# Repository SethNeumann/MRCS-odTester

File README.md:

# MRCS-odTester
## License: Creative Commons Attribution-NonCommercial-ShareAlike

A simple bench test board for Chubb\'s DCC-OD and MRCS\' cpOD detectors.

### Theory:

This board is designed to be a bench test unit for Chubb\'s DCCOD style
detectors. A board is inserted into the test pins and the three buttons
are pressed in sequence while observing the \"detected\" LED. A \"good\"
board will light up with both the \"low\" and \"normal\" button presses,
but not the \"high\" one. The DCCOD sensitivity can be adjusted in the
jig to give the desired behavior.

A local test track can be optionally connected that enables the testing
of specific locomotives and rolling stock simply by placing them on the
track.

The values for R1, R2 and R3 should be chosen for the layout and
locomotives in use - N-scale\'s small highly efficient motors will draw
less current than a O- or G-scale, and will require greater sensitivity.
Your wheelsets may provide 10K or 100K resistors, which should also
inform your choices. The values below are astarting point; feel free to
experiment. There is nothing wrong with choosing 100K as \"normal\" and
150K as \"too high\" as long as your choice of \"turns\" thru the
DCCOD\'s pulse transformer can provide the detection. Start with
\"normal\" matching your wheelset/rolling stock resistors, \"low\" being
half of that, and high being 2x to 10x of normal\...

Validate that your DCCOD can actually detect your chosen values by
adjusting its potentiometer to its mose sensitive position and observing
that the detected LED lights when the buttons are pressed.

Usage:

  -   Plug a DCCOD board to the DetectorTester.
  -   Connect to a 12v DC regulated power supply.
  -   Connect the output of a DCC booster to the DCC connector
  -   Press one of the pushbuttons to place a detectable load resistance across the simulated \"track\" for the detector to see
    -   Sensitivity test values (choose to match your givens and druthers)
    -   5K resistance (\~3mA)
    -   10K resistance (\~1.5mA)
    -   100K resistance (\~0.15mA)
    -   150K resistance (\~0.1mA)

Use the following table to diagnose/adjust based on the whether the
detection LED lights when the following buttons are pressed:

| LOW | NORMAL | HIGH  | |
|:----|:-------|:------|:----------------------------------------------------------------------------------------------------------------------------|
| OFF | OFF    | OFF   | Nothing lights, missing DCCOD, no DCC power, no DC power, poorly chosen R1,R2 and R3|
|----
| OFF | OFF    | ON    | Bad detector tester - check solder connections|
|----
| OFF | ON     | OFF   | Bad detector tester - check solder connections|
|----
| OFF | ON     | ON    | Bad detector board - check solder connections|
|----
| ON  | OFF    | OFF   | this DCCOD will have problems detecting a typical car resistance. Adjust DCCOD until NORMAL lights when pressed|
|----
| ON  | OFF    | ON    | Bad detector tester - check solder connections|
|----
| ON  | ON     | OFF   | this DCCOD is properly adjusted|
|----
| ON  | ON     | ON    | this DCCOD is potentially overly sensitive, and may false trigger. Lower the DCCOD sensitivity until this just extinguishes|
|====

If any of the LEDs light when no buttons are pressed and nothing is connected to the external track connector, either the detector tester or the DCCOD is bad.

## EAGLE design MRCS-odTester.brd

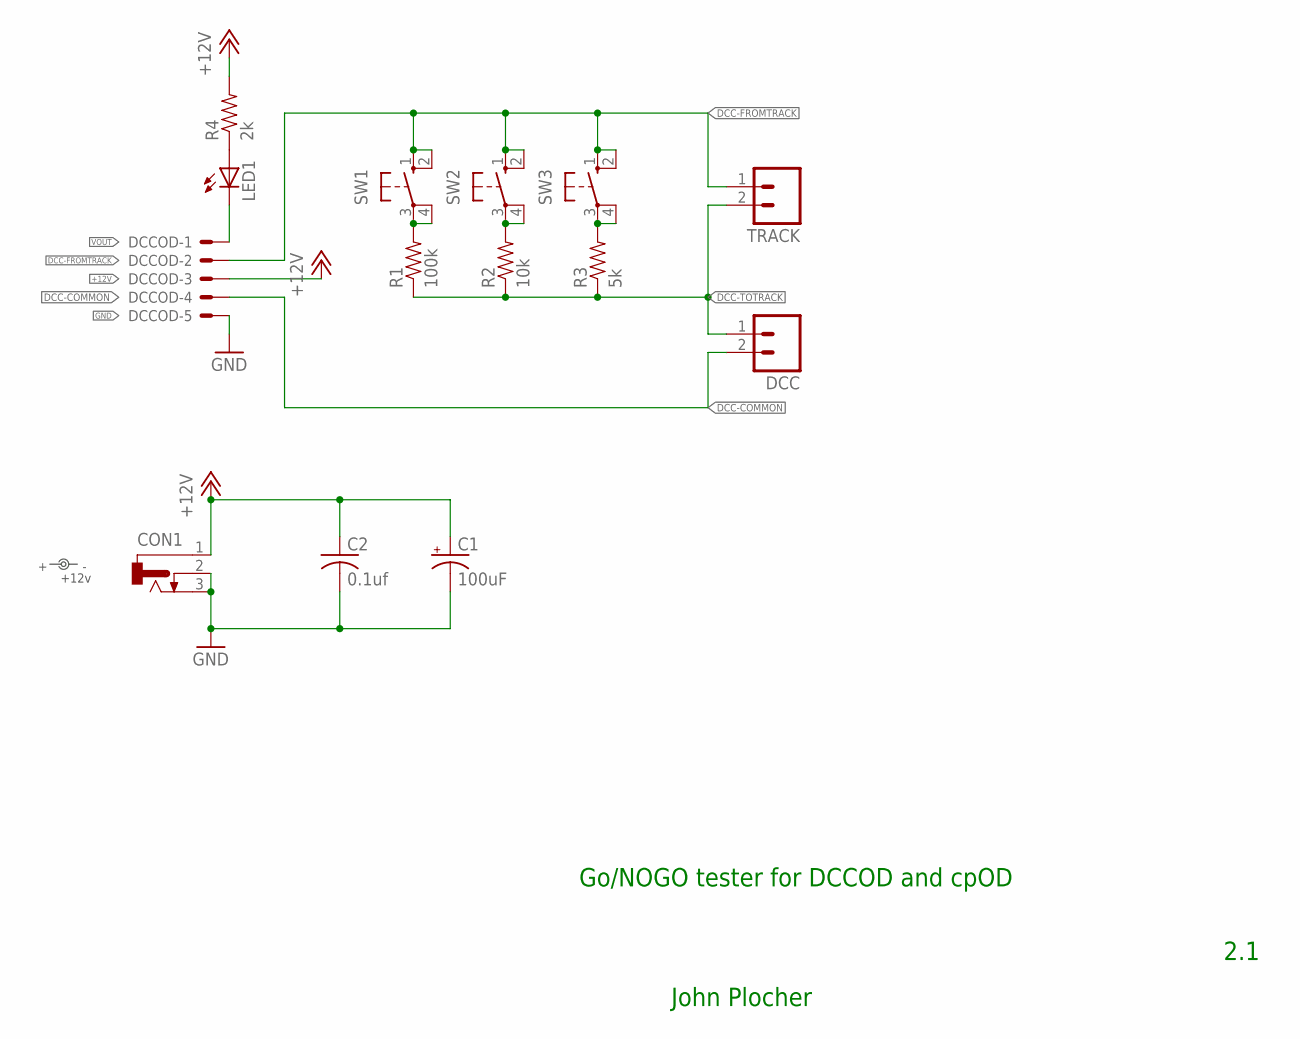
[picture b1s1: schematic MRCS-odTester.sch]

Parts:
C1: 100uF; E3.5-10
C2: 0.1uf; C050-024X044
CON1: CONNECTOR-DC-POWER-RA; DCJ0202
DCC: CONNECTOR-M02508-LOCK; MSTB2
DCCOD: KK-156-5
LED1: LEDLED5MM; LED5MM
R1: 100k; AXIAL-0.4-RES
R2: 10k; AXIAL-0.4-RES
R3: 5k; AXIAL-0.4-RES
R4: 2k; AXIAL-0.4-RES
SW1, SW2, SW3: SWITCH-10-XX; B3F-10XX
TRACK: CONNECTOR-M02508-LOCK; MSTB2
U$1: +12v; PWR_LABEL

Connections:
+12V: C1.+, C2.1, CON1.1, DCCOD.3, R4.P$2 (2)
DCC-COMMON: DCC.2 (B), DCCOD.4
DCC-FROMTRACK: DCCOD.2, SW1.1 (S), SW1.2 (S1), SW2.1 (S), SW2.2 (S1), SW3.1 (S), SW3.2 (S1), TRACK.1 (A)
DCC-TOTRACK: DCC.1 (A), R1.P$1 (1), R2.P$1 (1), R3.P$1 (1), TRACK.2 (B)
GND: C1.-, C2.2, CON1.2, CON1.3, DCCOD.5
unnamed: R1.P$2 (2), SW1.3, SW1.4 (P1)
unnamed: R2.P$2 (2), SW2.3, SW2.4 (P1)
unnamed: R3.P$2 (2), SW3.3, SW3.4 (P1)
unnamed: LED1.A, R4.P$1 (1)
VOUT: DCCOD.1, LED1.K (C)

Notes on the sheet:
Go/NOGO tester for DCCOD and cpOD
2.1
John Plocher

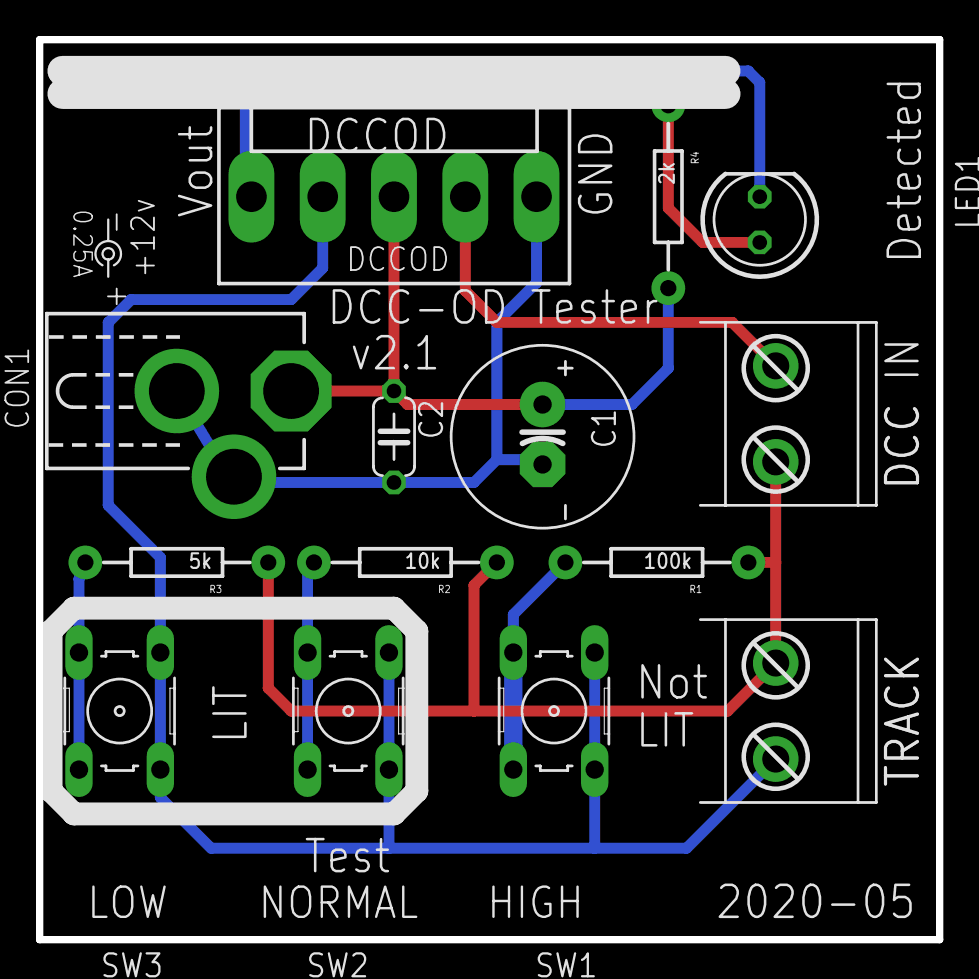
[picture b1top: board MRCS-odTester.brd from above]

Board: 2 copper layers, 50.0 x 50.0 mm, 15 parts (0 on the bottom side), 10 nets.

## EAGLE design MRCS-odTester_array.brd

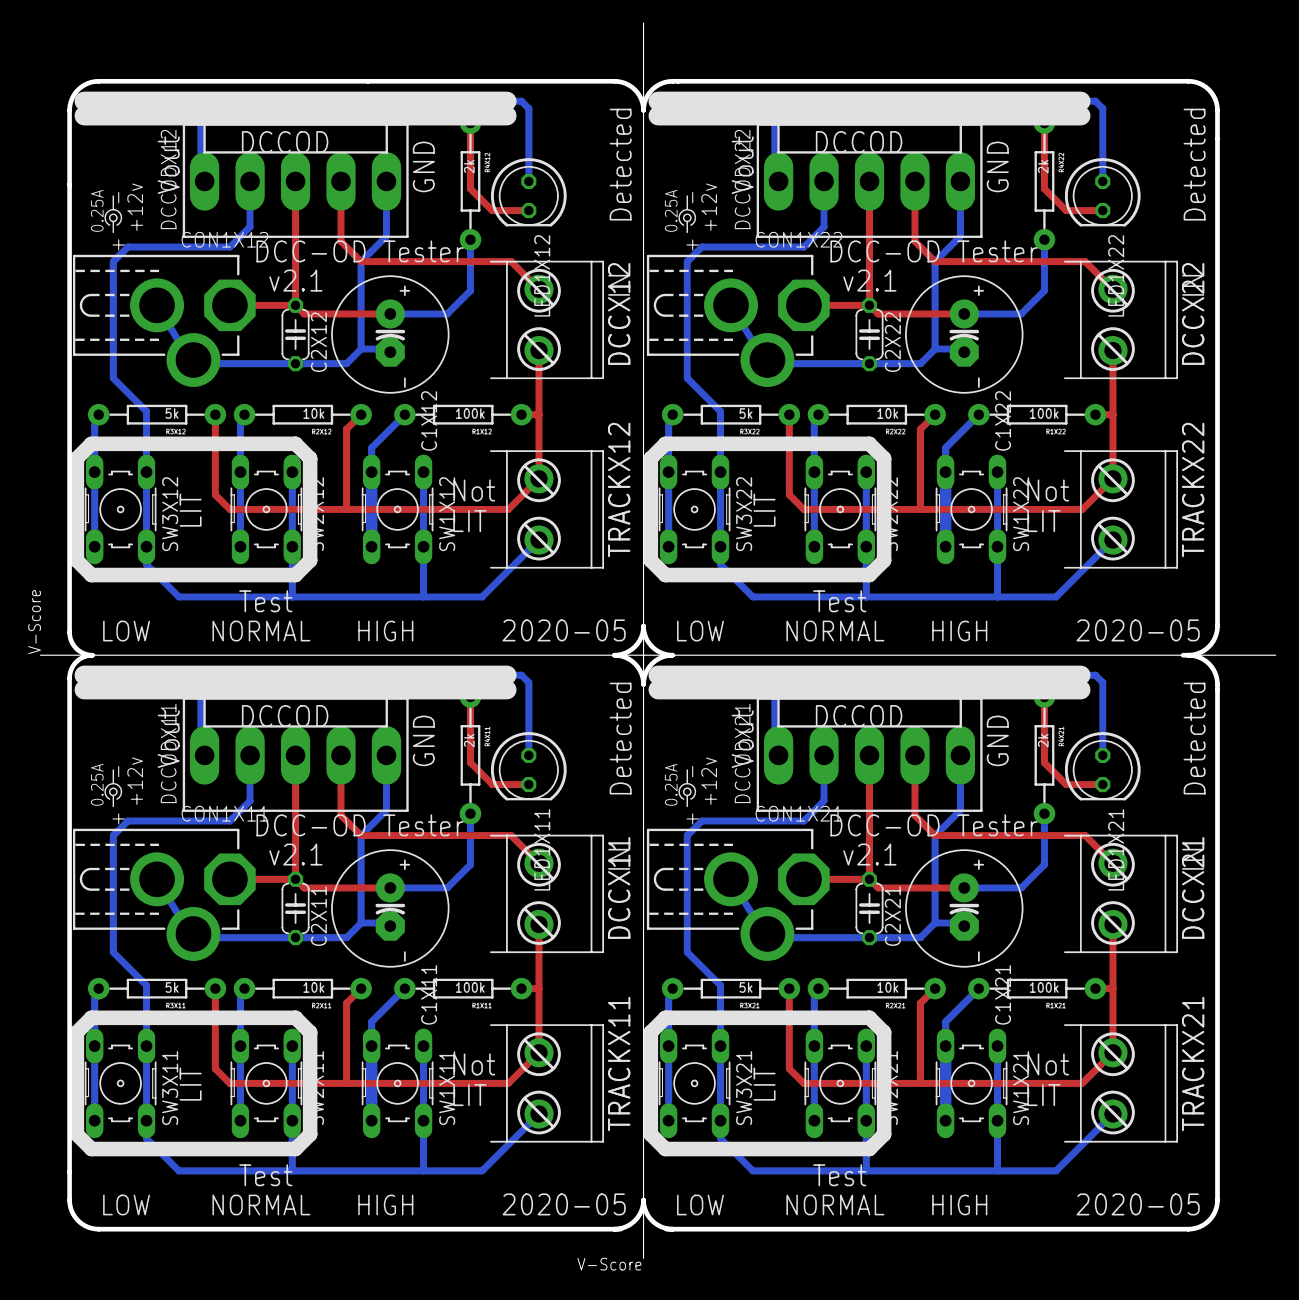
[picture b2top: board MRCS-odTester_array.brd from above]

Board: 2 copper layers, 108.7 x 108.8 mm, 61 parts (0 on the bottom side), 40 nets.

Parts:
C1X11, C1X12, C1X21, C1X22: 100uF; E3.5-10
C2X11, C2X12, C2X21, C2X22: 0.1uf; C050-024X044
CON1X11, CON1X12, CON1X21, CON1X22: DCJ0202
DCCODX11, DCCODX12, DCCODX21, DCCODX22: KK-156-5
DCCX11, DCCX12, DCCX21, DCCX22: MSTB2
LED1X11, LED1X12, LED1X21, LED1X22: LED5MM
R1X11, R1X12, R1X21, R1X22: 100k; AXIAL-0.4-RES
R2X11, R2X12, R2X21, R2X22: 10k; AXIAL-0.4-RES
R3X11, R3X12, R3X21, R3X22: 5k; AXIAL-0.4-RES
R4X11, R4X12, R4X21, R4X22: 2k; AXIAL-0.4-RES
SW1X11, SW1X12, SW1X21, SW1X22, SW2X11, SW2X12, SW2X21, SW2X22, SW3X11, SW3X12, SW3X21, SW3X22: B3F-10XX
TRACKX11, TRACKX12, TRACKX21, TRACKX22: MSTB2
U$1X1: BOARD-10X10-2X2-PANEL-R
U$1X11, U$1X12, U$1X21, U$1X22: +12v; PWR_LABEL

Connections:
+12VX11: C1X11.+, C2X11.1, CON1X11.1, DCCODX11.3, R4X11.P$2
+12VX12: C1X12.+, C2X12.1, CON1X12.1, DCCODX12.3, R4X12.P$2
+12VX21: C1X21.+, C2X21.1, CON1X21.1, DCCODX21.3, R4X21.P$2
+12VX22: C1X22.+, C2X22.1, CON1X22.1, DCCODX22.3, R4X22.P$2
DCC-COMMONX11: DCCODX11.4, DCCX11.2
DCC-COMMONX12: DCCODX12.4, DCCX12.2
DCC-COMMONX21: DCCODX21.4, DCCX21.2
DCC-COMMONX22: DCCODX22.4, DCCX22.2
DCC-FROMTRACKX11: DCCODX11.2, SW1X11.1, SW1X11.2, SW2X11.1, SW2X11.2, SW3X11.1, SW3X11.2, TRACKX11.1
DCC-FROMTRACKX12: DCCODX12.2, SW1X12.1, SW1X12.2, SW2X12.1, SW2X12.2, SW3X12.1, SW3X12.2, TRACKX12.1
DCC-FROMTRACKX21: DCCODX21.2, SW1X21.1, SW1X21.2, SW2X21.1, SW2X21.2, SW3X21.1, SW3X21.2, TRACKX21.1
DCC-FROMTRACKX22: DCCODX22.2, SW1X22.1, SW1X22.2, SW2X22.1, SW2X22.2, SW3X22.1, SW3X22.2, TRACKX22.1
DCC-TOTRACKX11: DCCX11.1, R1X11.P$1, R2X11.P$1, R3X11.P$1, TRACKX11.2
DCC-TOTRACKX12: DCCX12.1, R1X12.P$1, R2X12.P$1, R3X12.P$1, TRACKX12.2
DCC-TOTRACKX21: DCCX21.1, R1X21.P$1, R2X21.P$1, R3X21.P$1, TRACKX21.2
DCC-TOTRACKX22: DCCX22.1, R1X22.P$1, R2X22.P$1, R3X22.P$1, TRACKX22.2
GNDX11: C1X11.-, C2X11.2, CON1X11.2, CON1X11.3, DCCODX11.5
GNDX12: C1X12.-, C2X12.2, CON1X12.2, CON1X12.3, DCCODX12.5
GNDX21: C1X21.-, C2X21.2, CON1X21.2, CON1X21.3, DCCODX21.5
GNDX22: C1X22.-, C2X22.2, CON1X22.2, CON1X22.3, DCCODX22.5
unnamed: R1X11.P$2, SW1X11.3, SW1X11.4
unnamed: R1X12.P$2, SW1X12.3, SW1X12.4
unnamed: R1X21.P$2, SW1X21.3, SW1X21.4
unnamed: R1X22.P$2, SW1X22.3, SW1X22.4
unnamed: R2X11.P$2, SW2X11.3, SW2X11.4
unnamed: R2X12.P$2, SW2X12.3, SW2X12.4
unnamed: R2X21.P$2, SW2X21.3, SW2X21.4
unnamed: R2X22.P$2, SW2X22.3, SW2X22.4
unnamed: R3X11.P$2, SW3X11.3, SW3X11.4
unnamed: R3X12.P$2, SW3X12.3, SW3X12.4
unnamed: R3X21.P$2, SW3X21.3, SW3X21.4
unnamed: R3X22.P$2, SW3X22.3, SW3X22.4
unnamed: LED1X11.A, R4X11.P$1
unnamed: LED1X12.A, R4X12.P$1
unnamed: LED1X21.A, R4X21.P$1
unnamed: LED1X22.A, R4X22.P$1
VOUTX11: DCCODX11.1, LED1X11.K
VOUTX12: DCCODX12.1, LED1X12.K
VOUTX21: DCCODX21.1, LED1X21.K
VOUTX22: DCCODX22.1, LED1X22.K

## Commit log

2019-11-25 fixed table formatting
2019-11-27 fixed table presentation (md)
2019-11-28 ensured License is CC-NC-SA
2020-05-04 silkscreen cleanup
2020-10-14 created 2x2 panel
2020-12-20 changes to gitignore
    cleaned out work and derivative files
